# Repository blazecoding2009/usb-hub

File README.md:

# USB Hub
Simple USB Hub made in KiCad! It should allow for 400MBPS down/up on each port and upto 500ma power!

It should cost around $15 for each PCB! I'll be using [OnBoard](https://hack.af/onboard) to print this out!

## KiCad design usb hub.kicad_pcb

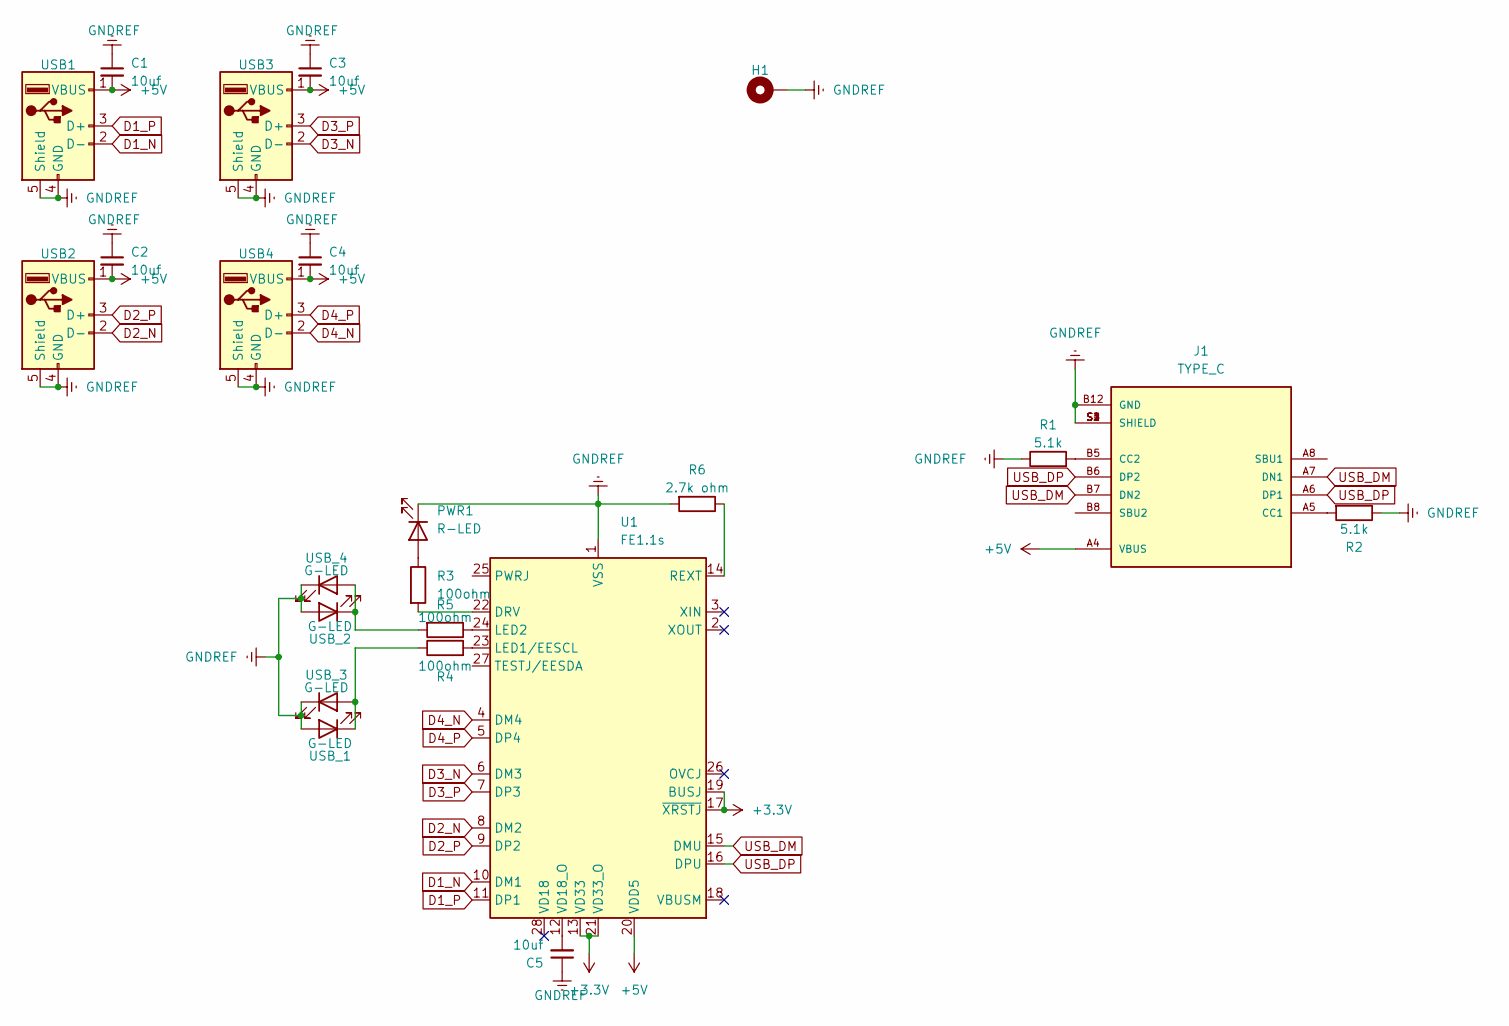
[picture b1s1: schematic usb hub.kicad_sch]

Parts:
C1, C2, C3, C4, C5: 10uf; C_0201_0603Metric
H1: MountingHole_Pad; MountingHole_2.2mm_M2_Pad_TopBottom
J1: TYPE_C; USB_C_Receptacle_HRO_TYPE-C-31-M-12; PARTREV 2020.12.08
PWR1: R-LED; D_0201_0603Metric
R1, R2: 5.1k; R_01005_0402Metric
R3, R4, R5: 100ohm; R_0201_0603Metric
R6: 2.7k ohm; R_0201_0603Metric
U1: FE1.1s; SSOP-28_3.9x9.9mm_P0.635mm
USB1, USB2, USB3, USB4: USB_A; USB_A_Receptacle_GCT_USB1046
USB_1, USB_2, USB_3, USB_4: G-LED; D_0201_0603Metric

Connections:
+3.3V: U1.13 (VD33), U1.17 (~XRSTJ), U1.19 (BUSJ), U1.21 (VD33_O)
+5V: C1.2, C2.2, C3.2, C4.2, J1.A4 (VBUS), J1.A9 (VBUS), J1.B4 (VBUS), J1.B9 (VBUS), U1.20 (VDD5), USB1.1 (VBUS), USB2.1 (VBUS), USB3.1 (VBUS), USB4.1 (VBUS)
D1_N: U1.10 (DM1), USB1.2 (D-)
D1_P: U1.11 (DP1), USB1.3 (D+)
D2_N: U1.8 (DM2), USB2.2 (D-)
D2_P: U1.9 (DP2), USB2.3 (D+)
D3_N: U1.6 (DM3), USB3.2 (D-)
D3_P: U1.7 (DP3), USB3.3 (D+)
D4_N: U1.4 (DM4), USB4.2 (D-)
D4_P: U1.5 (DP4), USB4.3 (D+)
GNDREF: C1.1, C2.1, C3.1, C4.1, C5.1, H1.1, J1.A1 (GND), J1.A12 (GND), J1.B1 (GND), J1.B12 (GND), J1.S1 (SHIELD), J1.S2 (SHIELD), J1.S3 (SHIELD), J1.S4 (SHIELD), PWR1.1 (K), R1.1, R2.1, R6.2, U1.1 (VSS), USB1.4 (GND), USB1.5 (Shield), USB2.4 (GND), USB2.5 (Shield), USB3.4 (GND), USB3.5 (Shield), USB4.4 (GND), USB4.5 (Shield), USB_1.2 (A), USB_2.2 (A), USB_3.1 (K), USB_4.1 (K)
unnamed: J1.A5 (CC1), R2.2
unnamed: J1.B5 (CC2), R1.2
unnamed: PWR1.2 (A), R3.1
unnamed: R3.2, U1.22 (DRV)
unnamed: R4.2, U1.23 (LED1/EESCL)
unnamed: R5.1, U1.24 (LED2)
unnamed: R6.1, U1.14 (REXT)
unnamed: C5.2, U1.12 (VD18_O)
unnamed: R4.1, USB_1.1 (K), USB_3.2 (A)
unnamed: R5.2, USB_2.1 (K), USB_4.2 (A)
USB_DM: J1.A7 (DN1), J1.B7 (DN2), U1.15 (DMU)
USB_DP: J1.A6 (DP1), J1.B6 (DP2), U1.16 (DPU)

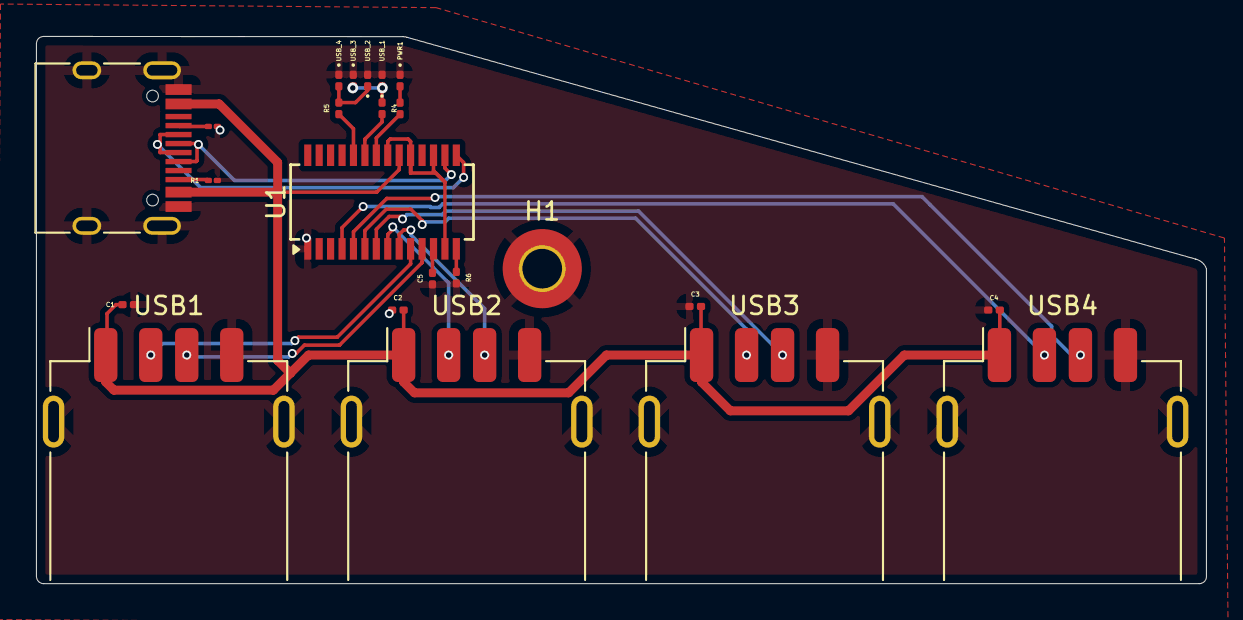
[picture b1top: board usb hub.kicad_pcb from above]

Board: 2 copper layers, 65.0 x 30.4 mm, 23 parts (0 on the bottom side), 23 nets.

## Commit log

2024-08-12 imit commit!
2024-08-13 more updates!
2024-08-13 yay sch finito
2024-08-13 a bit of part placemnt
2024-08-13 all routes fixed AND placed parts
2024-08-13 bit of routing
2024-08-13 aaaaaaaaa
2024-08-13 ITS FINISHED!!!
2024-08-13 pushing some files i forgot
2024-08-18 fixed some sch stuff, need to add holes still
2024-08-19 holes
